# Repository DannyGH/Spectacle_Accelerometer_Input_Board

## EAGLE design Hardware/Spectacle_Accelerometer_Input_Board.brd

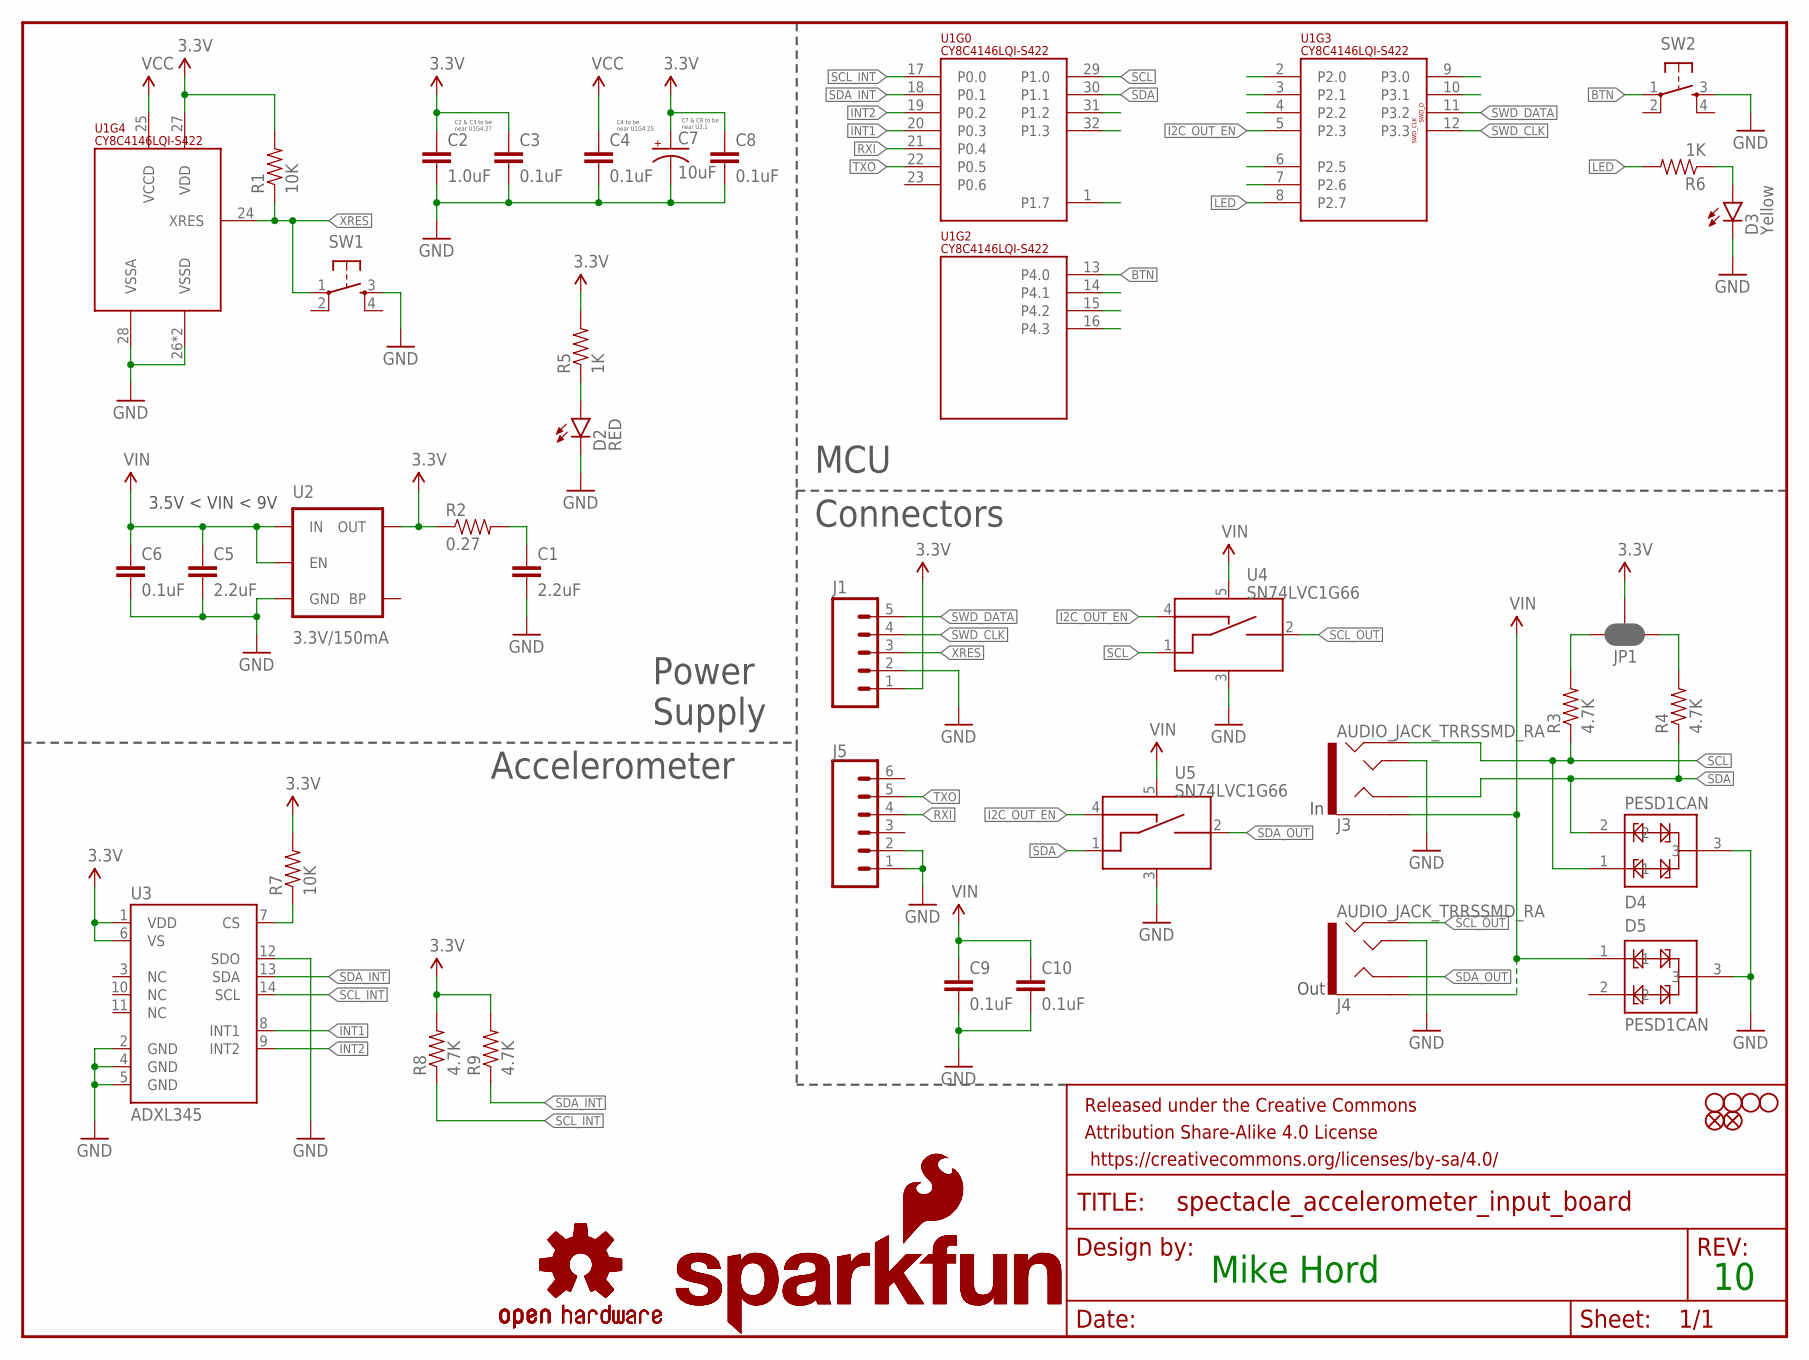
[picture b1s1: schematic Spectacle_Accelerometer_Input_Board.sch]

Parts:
C1, C5: 2.2uF; 0603-CAP
C2: 1.0uF; 0402-CAP
C3, C4, C6, C8, C9, C10: 0.1uF; 0402-CAP
C7: 10uF; EIA3216
D2: RED; LED-0603
D3: Yellow; LED-0603
D4, D5: PESD1CAN; SOT23-3
FD1, FD2: FIDUCIALUFIDUCIAL; MICRO-FIDUCIAL
FRAME1: FRAME-LETTER; CREATIVE_COMMONS
H1, H2, H3, H4: STAND-OFF
J1: M05NO_SILK; 1X05_NO_SILK
J3, J4: AUDIO_JACK_TRRSSMD_RA; AUDIO_JACK_3.5MM_TRRS_SMD_RA
J5: CONN_06NO_SILK_NO_POP; 1X06_NO_SILK
JP1: JUMPER-PAD-3-NC_BY_PASTE; PAD-JUMPER-3-NC_BY_PASTE_YES_SILK_FULL_BOX
LOGO1, LOGO4: SFE_LOGO_NAME_FLAME.1_INCH; SFE_LOGO_NAME_FLAME_.1
LOGO2, LOGO3: OSHW-LOGOS; OSHW-LOGO-S
R1, R7: 10K; 0603-RES
R2: 0.27; 0603-RES
R3, R4, R8, R9: 4.7K; 0603-RES
R5, R6: 1K; 0603-RES
SW1, SW2: SWITCH_SPST_4_PINRECT; TACTILE_SWITCH_SMD_4.6X2.8MM
U1: CY8C4146LQI-S422; QFN-32
U2: 3.3V/150mA; SOT23-5
U3: ADXL345; ADXL3451:1
U4, U5: SN74LVC1G66; SOT23-5

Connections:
3.3V: C2.1, C3.1, C7.A (+), C8.1, J1.1, JP1.2, R1.2, R2.1, R5.2, R7.2, R8.2, R9.2, U1.27 (VDD), U2.5 (OUT), U3.1 (VDD), U3.6 (VS)
BTN: SW2.1, U1.13 (P4.0)
GND: C1.2, C2.2, C3.2, C4.2, C5.2, C6.2, C7.C (-), C8.2, C9.2, C10.2, D2.C, D3.C, D4.3, D5.3, J1.2, J3.TIP, J4.TIP, J5.1, J5.2, SW1.3, SW2.3, U1.26 (VSSD), U1.28 (VSSA), U1.EP (VSSD), U2.2 (GND), U3.2 (GND), U3.4 (GND), U3.5 (GND), U3.12 (SDO), U4.3 (VSS), U5.3 (VSS)
I2C_OUT_EN: U1.5 (P2.3), U4.4 (CTRL_IN), U5.4 (CTRL_IN)
INT1: U1.20 (P0.3), U3.8 (INT1)
INT2: U1.19 (P0.2), U3.9 (INT2)
LED: R6.2, U1.8 (P2.7)
unnamed: JP1.3, R3.2
unnamed: C1.1, R2.2
unnamed: D2.A, R5.1
unnamed: D3.A, R6.1
unnamed: JP1.1, R4.2
unnamed: R7.1, U3.7 (CS)
RXI: J5.4, U1.21 (P0.4)
SCL: D4.1, J3.RING2, R3.1, U1.29 (P1.0), U4.1 (A_IN)
SCL_INT: R8.1, U1.17 (P0.0), U3.14 (SCL)
SCL_OUT: J4.RING2, U4.2 (A_OUT)
SDA: D4.2, J3.RING1, R4.1, U1.30 (P1.1), U5.1 (A_IN)
SDA_INT: R9.1, U1.18 (P0.1), U3.13 (SDA)
SDA_OUT: J4.RING1, U5.2 (A_OUT)
SWD_CLK: J1.4, U1.12 (P3.3)
SWD_DATA: J1.5, U1.11 (P3.2)
TXO: J5.5, U1.22 (P0.5)
VCC: C4.1, U1.25 (VCCD)
VIN: C5.1, C6.1, C9.1, C10.1, D5.1, J3.EARTH, J4.EARTH, U2.1 (IN), U2.3 (EN), U4.5 (VCC), U5.5 (VCC)
XRES: J1.3, R1.1, SW1.1, U1.24 (XRES)

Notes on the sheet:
C2 & C3 to be near U1G4.27
C4 to be near U1G4.25
C7 & C8 to be near U3.1
Mike Hord
Connectors
Accelerometer
MCU
Power Supply
3.5V < VIN < 9V
Out

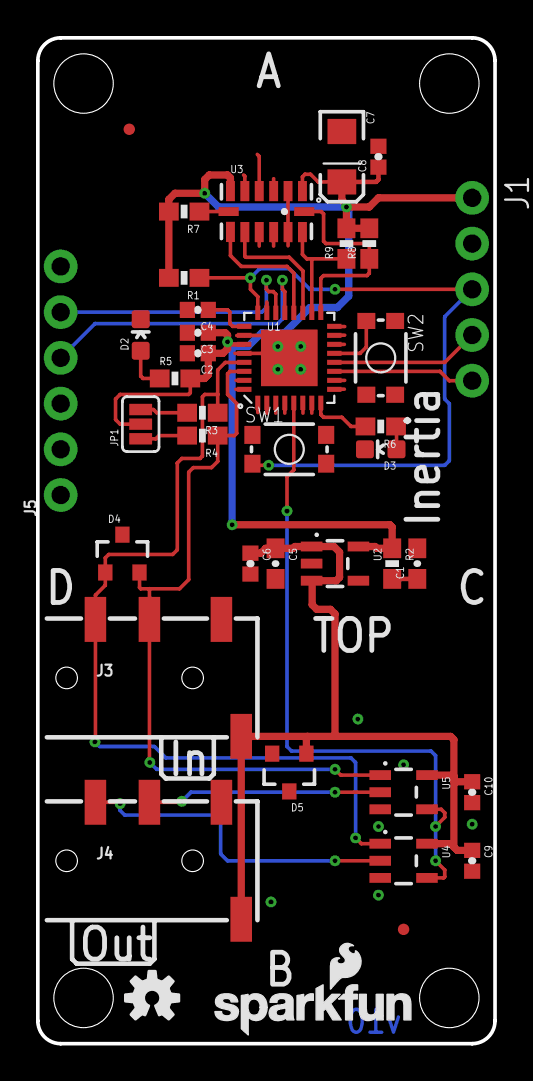
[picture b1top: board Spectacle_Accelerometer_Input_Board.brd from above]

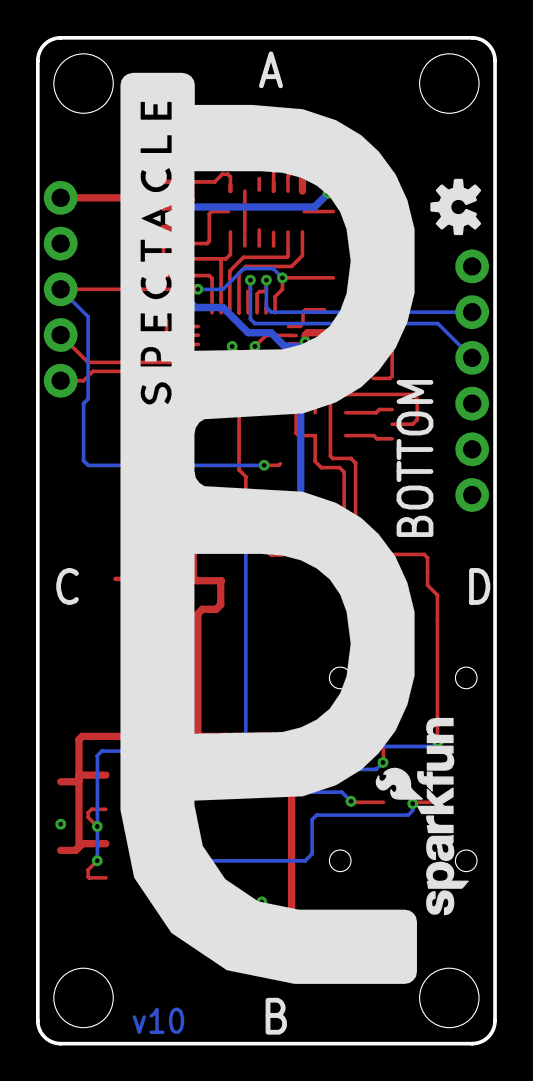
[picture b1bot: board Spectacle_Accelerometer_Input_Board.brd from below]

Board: 2 copper layers, 25.4 x 55.9 mm, 47 parts (3 on the bottom side), 26 nets.

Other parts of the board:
U$4: SPECTACLE_LOGO_NEGATIVE_2.2X1.0

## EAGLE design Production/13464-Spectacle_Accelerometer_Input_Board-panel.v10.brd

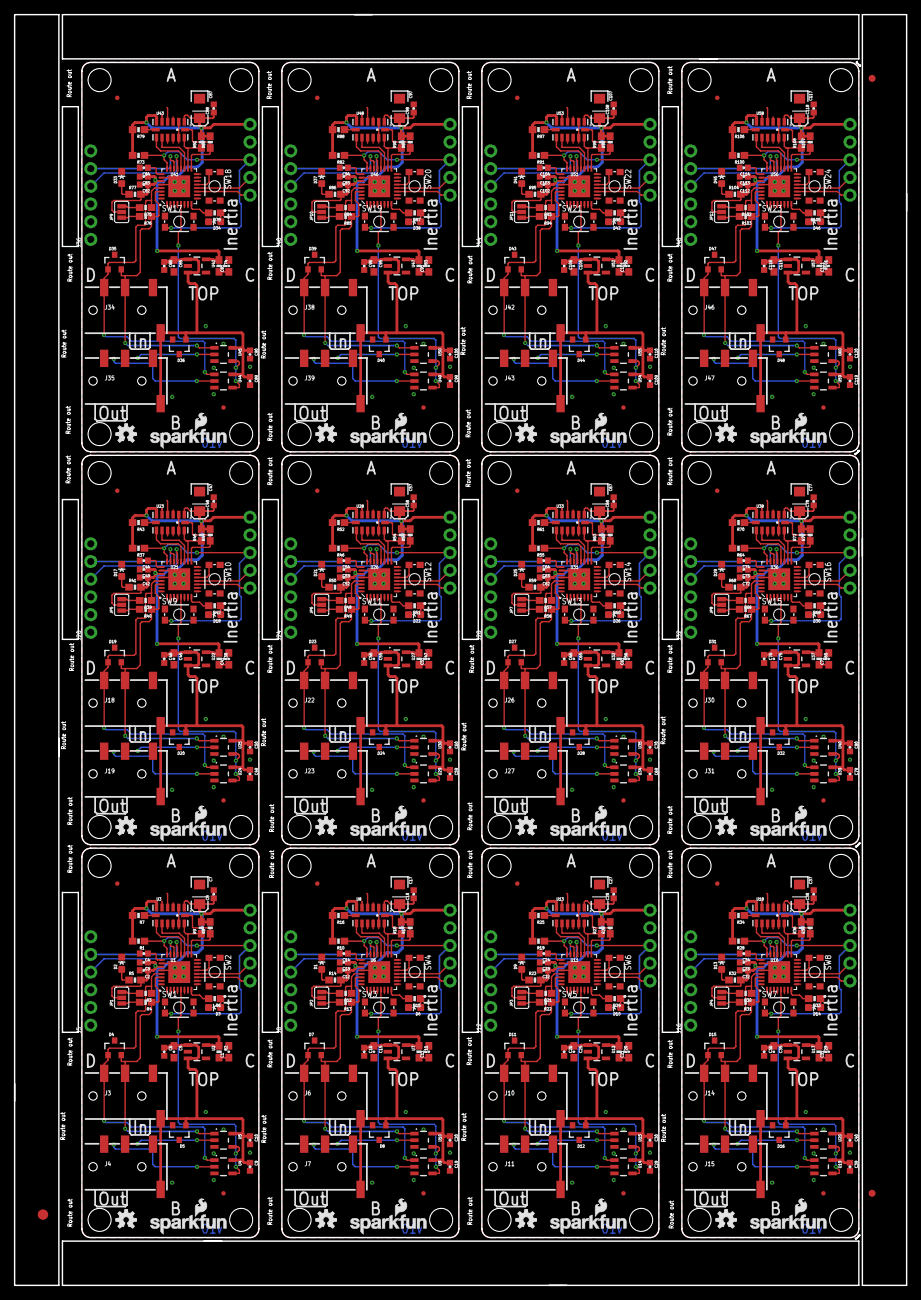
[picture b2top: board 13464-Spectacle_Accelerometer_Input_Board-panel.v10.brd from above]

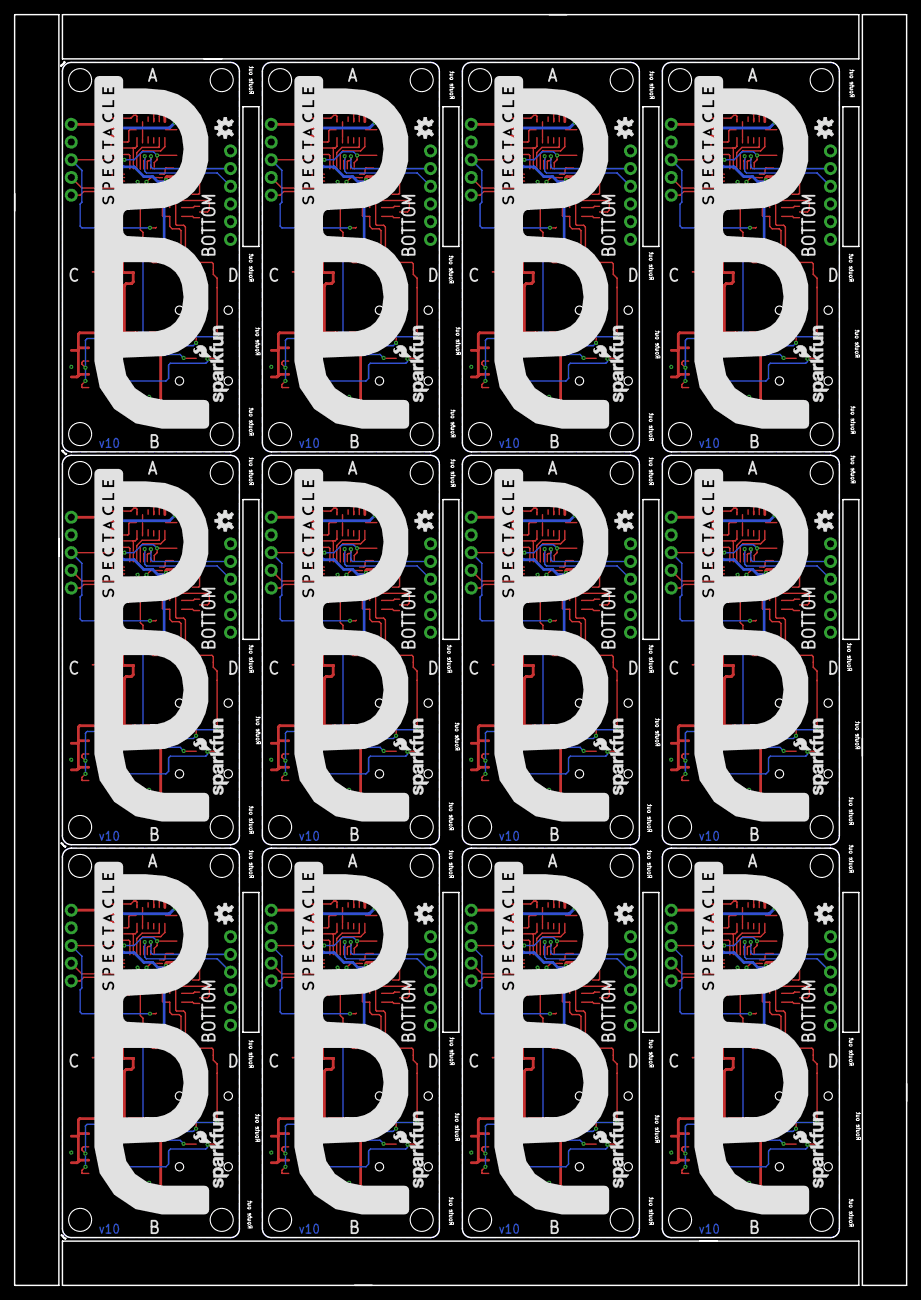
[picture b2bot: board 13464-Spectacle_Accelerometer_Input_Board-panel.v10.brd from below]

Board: 2 copper layers, 128.0 x 182.4 mm, 555 parts (36 on the bottom side), 312 nets.

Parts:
C1, C5, C11, C15, C21, C25, C31, C35, C41, C45, C51, C55, C61, C65, C71, C75, C81, C85, C91, C95, C101, C105, C111, C115: 2.2uF; 0603-CAP
C2, C12, C22, C32, C42, C52, C62, C72, C82, C92, C102, C112: 1.0uF; 0402-CAP
C3, C4, C6, C8, C9, C10, C13, C14, C16, C18, C19, C20, C23, C24, C26, C28, C29, C30, C33, C34, C36, C38, C39, C40, C43, C44, C46, C48, C49, C50, C53, C54, C56, C58, C59, C60, C63, C64, C66, C68, C69, C70, C73, C74, C76, C78, C79, C80, C83, C84, C86, C88, C89, C90, C93, C94, C96, C98, C99, C100, C103, C104, C106, C108, C109, C110, C113, C114, C116, C118, C119, C120: 0.1uF; 0402-CAP
C7, C17, C27, C37, C47, C57, C67, C77, C87, C97, C107, C117: 10uF; EIA3216
D1, D2, D9, D13, D17, D21, D25, D29, D33, D37, D41, D45: RED; LED-0603
D3, D6, D10, D14, D18, D22, D26, D30, D34, D38, D42, D46: Yellow; LED-0603
D4, D5, D7, D8, D11, D12, D15, D16, D19, D20, D23, D24, D27, D28, D31, D32, D35, D36, D39, D40, D43, D44, D47, D48: PESD1CAN; SOT23-3
E$1: FIDUCIAL-1.5X3
E$5, E$6: FIDUCIAL-1X2
FD1, FD2, FD3, FD4, FD5, FD6, FD7, FD8, FD9, FD10, FD11, FD12, FD13, FD14, FD15, FD16, FD17, FD18, FD19, FD20, FD21, FD22, FD23, FD24: FIDUCIALUFIDUCIAL; MICRO-FIDUCIAL
H1, H2, H3, H4, H5, H6, H7, H8, H9, H10, H11, H12, H13, H14, H15, H16, H17, H18, H19, H20, H21, H22, H23, H24, H25, H26, H27, H28, H29, H30, H31, H32, H33, H34, H35, H36, H37, H38, H39, H40, H41, H42, H43, H44, H45, H46, H47, H48: STAND-OFF
J1, J2, J9, J13, J17, J21, J25, J29, J33, J37, J41, J45: 1X05_NO_SILK
J3, J4, J6, J7, J10, J11, J14, J15, J18, J19, J22, J23, J26, J27, J30, J31, J34, J35, J38, J39, J42, J43, J46, J47: AUDIO_JACK_TRRSSMD_RA; AUDIO_JACK_3.5MM_TRRS_SMD_RA
J5, J8, J12, J16, J20, J24, J28, J32, J36, J40, J44, J48: 1X06_NO_SILK
JP1, JP2, JP3, JP4, JP5, JP6, JP7, JP8, JP9, JP10, JP11, JP12: JUMPER-PAD-3-NC_BY_PASTE; PAD-JUMPER-3-NC_BY_PASTE_YES_SILK_FULL_BOX
LOGO1, LOGO4, LOGO5, LOGO8, LOGO9, LOGO12, LOGO13, LOGO16, LOGO17, LOGO20, LOGO21, LOGO24, LOGO25, LOGO28, LOGO29, LOGO32, LOGO33, LOGO36, LOGO37, LOGO40, LOGO41, LOGO44, LOGO45, LOGO48: SFE_LOGO_NAME_FLAME.1_INCH; SFE_LOGO_NAME_FLAME_.1
LOGO2, LOGO3, LOGO6, LOGO7, LOGO10, LOGO11, LOGO14, LOGO15, LOGO18, LOGO19, LOGO22, LOGO23, LOGO26, LOGO27, LOGO30, LOGO31, LOGO34, LOGO35, LOGO38, LOGO39, LOGO42, LOGO43, LOGO46, LOGO47: OSHW-LOGOS; OSHW-LOGO-S
R1, R7, R10, R16, R19, R25, R28, R34, R37, R43, R46, R52, R55, R61, R64, R70, R73, R79, R82, R88, R91, R97, R100, R106: 10K; 0603-RES
R2, R11, R20, R29, R38, R47, R56, R65, R74, R83, R92, R101: 0.27; 0603-RES
R3, R4, R8, R9, R12, R13, R17, R18, R21, R22, R26, R27, R30, R31, R35, R36, R39, R40, R44, R45, R48, R49, R53, R54, R57, R58, R62, R63, R66, R67, R71, R72, R75, R76, R80, R81, R84, R85, R89, R90, R93, R94, R98, R99, R102, R103, R107, R108: 4.7K; 0603-RES
R5, R6, R14, R15, R23, R24, R32, R33, R41, R42, R50, R51, R59, R60, R68, R69, R77, R78, R86, R87, R95, R96, R104, R105: 1K; 0603-RES
SW1, SW2, SW3, SW4, SW5, SW6, SW7, SW8, SW9, SW10, SW11, SW12, SW13, SW14, SW15, SW16, SW17, SW18, SW19, SW20, SW21, SW22, SW23, SW24: TACTILE_SWITCH_SMD_4.6X2.8MM
U1, U6, U11, U16, U21, U26, U31, U36, U41, U46, U51, U56: CY8C4146LQI-S422; QFN-32
U2, U7, U12, U17, U22, U27, U32, U37, U42, U47, U52, U57: 3.3V/150mA; SOT23-5
U3, U8, U13, U18, U23, U28, U33, U38, U43, U48, U53, U58: ADXL345; ADXL3451:1
U4, U5, U9, U10, U14, U15, U19, U20, U24, U25, U29, U30, U34, U35, U39, U40, U44, U45, U49, U50, U54, U55, U59, U60: SN74LVC1G66; SOT23-5
U$1, U$2, U$3, U$4, U$5, U$6, U$7, U$8, U$9, U$10, U$11, U$12: SPECTACLE_LOGO_NEGATIVE_2.2X1.0

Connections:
3.3V: C2.1, C3.1, C7.A, C8.1, J1.1, JP1.2, R1.2, R2.1, R5.2, R7.2, R8.2, R9.2, U1.27, U2.5, U3.1, U3.6
3.3V1: C12.1, C13.1, C17.A, C18.1, J2.1, JP2.2, R10.2, R11.1, R14.2, R16.2, R17.2, R18.2, U6.27, U7.5, U8.1, U8.6
3.3V2: C22.1, C23.1, C27.A, C28.1, J9.1, JP3.2, R19.2, R20.1, R23.2, R25.2, R26.2, R27.2, U11.27, U12.5, U13.1, U13.6
3.3V3: C32.1, C33.1, C37.A, C38.1, J13.1, JP4.2, R28.2, R29.1, R32.2, R34.2, R35.2, R36.2, U16.27, U17.5, U18.1, U18.6
3.3V4: C42.1, C43.1, C47.A, C48.1, J17.1, JP5.2, R37.2, R38.1, R41.2, R43.2, R44.2, R45.2, U21.27, U22.5, U23.1, U23.6
3.3V5: C52.1, C53.1, C57.A, C58.1, J21.1, JP6.2, R46.2, R47.1, R50.2, R52.2, R53.2, R54.2, U26.27, U27.5, U28.1, U28.6
3.3V6: C62.1, C63.1, C67.A, C68.1, J25.1, JP7.2, R55.2, R56.1, R59.2, R61.2, R62.2, R63.2, U31.27, U32.5, U33.1, U33.6
3.3V7: C72.1, C73.1, C77.A, C78.1, J29.1, JP8.2, R64.2, R65.1, R68.2, R70.2, R71.2, R72.2, U36.27, U37.5, U38.1, U38.6
3.3V8: C82.1, C83.1, C87.A, C88.1, J33.1, JP9.2, R73.2, R74.1, R77.2, R79.2, R80.2, R81.2, U41.27, U42.5, U43.1, U43.6
3.3V9: C92.1, C93.1, C97.A, C98.1, J37.1, JP10.2, R82.2, R83.1, R86.2, R88.2, R89.2, R90.2, U46.27, U47.5, U48.1, U48.6
3.3V10: C102.1, C103.1, C107.A, C108.1, J41.1, JP11.2, R91.2, R92.1, R95.2, R97.2, R98.2, R99.2, U51.27, U52.5, U53.1, U53.6
3.3V11: C112.1, C113.1, C117.A, C118.1, J45.1, JP12.2, R100.2, R101.1, R104.2, R106.2, R107.2, R108.2, U56.27, U57.5, U58.1, U58.6
BTN: SW2.1, U1.13
BTN1: SW4.1, U6.13
BTN2: SW6.1, U11.13
BTN3: SW8.1, U16.13
BTN4: SW10.1, U21.13
BTN5: SW12.1, U26.13
BTN6: SW14.1, U31.13
BTN7: SW16.1, U36.13
BTN8: SW18.1, U41.13
BTN9: SW20.1, U46.13
BTN10: SW22.1, U51.13
BTN11: SW24.1, U56.13
GND: C1.2, C2.2, C3.2, C4.2, C5.2, C6.2, C7.C, C8.2, C9.2, C10.2, D2.C, D3.C, D4.3, D5.3, J1.2, J3.TIP, J4.TIP, J5.1, J5.2, SW1.3, SW2.3, U1.26, U1.28, U1.EP, U2.2, U3.2, U3.4, U3.5, U3.12, U4.3, U5.3
GND1: C11.2, C12.2, C13.2, C14.2, C15.2, C16.2, C17.C, C18.2, C19.2, C20.2, D1.C, D6.C, D7.3, D8.3, J2.2, J6.TIP, J7.TIP, J8.1, J8.2, SW3.3, SW4.3, U6.26, U6.28, U6.EP, U7.2, U8.2, U8.4, U8.5, U8.12, U9.3, U10.3
GND2: C21.2, C22.2, C23.2, C24.2, C25.2, C26.2, C27.C, C28.2, C29.2, C30.2, D9.C, D10.C, D11.3, D12.3, J9.2, J10.TIP, J11.TIP, J12.1, J12.2, SW5.3, SW6.3, U11.26, U11.28, U11.EP, U12.2, U13.2, U13.4, U13.5, U13.12, U14.3, U15.3
GND3: C31.2, C32.2, C33.2, C34.2, C35.2, C36.2, C37.C, C38.2, C39.2, C40.2, D13.C, D14.C, D15.3, D16.3, J13.2, J14.TIP, J15.TIP, J16.1, J16.2, SW7.3, SW8.3, U16.26, U16.28, U16.EP, U17.2, U18.2, U18.4, U18.5, U18.12, U19.3, U20.3
GND4: C41.2, C42.2, C43.2, C44.2, C45.2, C46.2, C47.C, C48.2, C49.2, C50.2, D17.C, D18.C, D19.3, D20.3, J17.2, J18.TIP, J19.TIP, J20.1, J20.2, SW9.3, SW10.3, U21.26, U21.28, U21.EP, U22.2, U23.2, U23.4, U23.5, U23.12, U24.3, U25.3
GND5: C51.2, C52.2, C53.2, C54.2, C55.2, C56.2, C57.C, C58.2, C59.2, C60.2, D21.C, D22.C, D23.3, D24.3, J21.2, J22.TIP, J23.TIP, J24.1, J24.2, SW11.3, SW12.3, U26.26, U26.28, U26.EP, U27.2, U28.2, U28.4, U28.5, U28.12, U29.3, U30.3
GND6: C61.2, C62.2, C63.2, C64.2, C65.2, C66.2, C67.C, C68.2, C69.2, C70.2, D25.C, D26.C, D27.3, D28.3, J25.2, J26.TIP, J27.TIP, J28.1, J28.2, SW13.3, SW14.3, U31.26, U31.28, U31.EP, U32.2, U33.2, U33.4, U33.5, U33.12, U34.3, U35.3
GND7: C71.2, C72.2, C73.2, C74.2, C75.2, C76.2, C77.C, C78.2, C79.2, C80.2, D29.C, D30.C, D31.3, D32.3, J29.2, J30.TIP, J31.TIP, J32.1, J32.2, SW15.3, SW16.3, U36.26, U36.28, U36.EP, U37.2, U38.2, U38.4, U38.5, U38.12, U39.3, U40.3
GND8: C81.2, C82.2, C83.2, C84.2, C85.2, C86.2, C87.C, C88.2, C89.2, C90.2, D33.C, D34.C, D35.3, D36.3, J33.2, J34.TIP, J35.TIP, J36.1, J36.2, SW17.3, SW18.3, U41.26, U41.28, U41.EP, U42.2, U43.2, U43.4, U43.5, U43.12, U44.3, U45.3
GND9: C91.2, C92.2, C93.2, C94.2, C95.2, C96.2, C97.C, C98.2, C99.2, C100.2, D37.C, D38.C, D39.3, D40.3, J37.2, J38.TIP, J39.TIP, J40.1, J40.2, SW19.3, SW20.3, U46.26, U46.28, U46.EP, U47.2, U48.2, U48.4, U48.5, U48.12, U49.3, U50.3
GND10: C101.2, C102.2, C103.2, C104.2, C105.2, C106.2, C107.C, C108.2, C109.2, C110.2, D41.C, D42.C, D43.3, D44.3, J41.2, J42.TIP, J43.TIP, J44.1, J44.2, SW21.3, SW22.3, U51.26, U51.28, U51.EP, U52.2, U53.2, U53.4, U53.5, U53.12, U54.3, U55.3
GND11: C111.2, C112.2, C113.2, C114.2, C115.2, C116.2, C117.C, C118.2, C119.2, C120.2, D45.C, D46.C, D47.3, D48.3, J45.2, J46.TIP, J47.TIP, J48.1, J48.2, SW23.3, SW24.3, U56.26, U56.28, U56.EP, U57.2, U58.2, U58.4, U58.5, U58.12, U59.3, U60.3
I2C_OUT_EN: U1.5, U4.4, U5.4
I2C_OUT_EN1: U6.5, U9.4, U10.4
I2C_OUT_EN2: U11.5, U14.4, U15.4
I2C_OUT_EN3: U16.5, U19.4, U20.4
I2C_OUT_EN4: U21.5, U24.4, U25.4
I2C_OUT_EN5: U26.5, U29.4, U30.4
I2C_OUT_EN6: U31.5, U34.4, U35.4
I2C_OUT_EN7: U36.5, U39.4, U40.4
I2C_OUT_EN8: U41.5, U44.4, U45.4
I2C_OUT_EN9: U46.5, U49.4, U50.4
I2C_OUT_EN10: U51.5, U54.4, U55.4
I2C_OUT_EN11: U56.5, U59.4, U60.4
INT1: U1.20, U3.8
INT2: U1.19, U3.9
INT3: U6.20, U8.8
INT4: U6.19, U8.9
INT5: U11.20, U13.8
INT6: U11.19, U13.9
INT7: U16.20, U18.8
INT8: U16.19, U18.9
INT9: U21.20, U23.8
INT10: U21.19, U23.9
INT11: U26.20, U28.8
INT12: U26.19, U28.9
INT13: U31.20, U33.8
INT14: U31.19, U33.9
INT15: U36.20, U38.8
INT16: U36.19, U38.9
INT17: U41.20, U43.8
INT18: U41.19, U43.9
INT19: U46.20, U48.8
INT20: U46.19, U48.9
INT21: U51.20, U53.8
INT22: U51.19, U53.9
INT23: U56.20, U58.8
INT24: U56.19, U58.9
LED: R6.2, U1.8
LED1: R15.2, U6.8
LED2: R24.2, U11.8
LED3: R33.2, U16.8
LED4: R42.2, U21.8
LED5: R51.2, U26.8
LED6: R60.2, U31.8
LED7: R69.2, U36.8
LED8: R78.2, U41.8
LED9: R87.2, U46.8
LED10: R96.2, U51.8
LED11: R105.2, U56.8
unnamed: JP1.3, R3.2
unnamed: C1.1, R2.2
unnamed: D2.A, R5.1
unnamed: D3.A, R6.1
unnamed: JP1.1, R4.2
unnamed: R7.1, U3.7
unnamed: C11.1, R11.2
unnamed: JP2.3, R12.2
unnamed: JP2.1, R13.2
unnamed: D1.A, R14.1
unnamed: D6.A, R15.1
unnamed: R16.1, U8.7
unnamed: C21.1, R20.2
unnamed: JP3.3, R21.2
unnamed: JP3.1, R22.2
unnamed: D9.A, R23.1
unnamed: D10.A, R24.1
unnamed: R25.1, U13.7
unnamed: C31.1, R29.2
unnamed: JP4.3, R30.2
unnamed: JP4.1, R31.2
unnamed: D13.A, R32.1
unnamed: D14.A, R33.1
unnamed: R34.1, U18.7
unnamed: C41.1, R38.2
unnamed: JP5.3, R39.2
unnamed: JP5.1, R40.2
unnamed: D17.A, R41.1
unnamed: D18.A, R42.1
unnamed: R43.1, U23.7
unnamed: C51.1, R47.2
unnamed: JP6.3, R48.2
unnamed: JP6.1, R49.2
unnamed: D21.A, R50.1
unnamed: D22.A, R51.1
unnamed: R52.1, U28.7
unnamed: C61.1, R56.2
unnamed: JP7.3, R57.2
unnamed: JP7.1, R58.2
unnamed: D25.A, R59.1
unnamed: D26.A, R60.1
unnamed: R61.1, U33.7
unnamed: C71.1, R65.2
unnamed: JP8.3, R66.2
unnamed: JP8.1, R67.2
unnamed: D29.A, R68.1
unnamed: D30.A, R69.1
unnamed: R70.1, U38.7
unnamed: C81.1, R74.2
unnamed: JP9.3, R75.2
unnamed: JP9.1, R76.2
unnamed: D33.A, R77.1
unnamed: D34.A, R78.1
unnamed: R79.1, U43.7
unnamed: C91.1, R83.2
unnamed: JP10.3, R84.2
unnamed: JP10.1, R85.2
unnamed: D37.A, R86.1
unnamed: D38.A, R87.1
unnamed: R88.1, U48.7
unnamed: C101.1, R92.2
unnamed: JP11.3, R93.2
unnamed: JP11.1, R94.2
unnamed: D41.A, R95.1
unnamed: D42.A, R96.1
unnamed: R97.1, U53.7
unnamed: C111.1, R101.2
unnamed: JP12.3, R102.2
unnamed: JP12.1, R103.2
unnamed: D45.A, R104.1
unnamed: D46.A, R105.1
unnamed: R106.1, U58.7
RXI: J5.4, U1.21
RXI1: J8.4, U6.21
RXI2: J12.4, U11.21
RXI3: J16.4, U16.21
RXI4: J20.4, U21.21
RXI5: J24.4, U26.21
RXI6: J28.4, U31.21
RXI7: J32.4, U36.21
RXI8: J36.4, U41.21
RXI9: J40.4, U46.21
RXI10: J44.4, U51.21
RXI11: J48.4, U56.21
SCL: D4.1, J3.RING2, R3.1, U1.29, U4.1
SCL1: D7.1, J6.RING2, R12.1, U6.29, U9.1
SCL2: D11.1, J10.RING2, R21.1, U11.29, U14.1
SCL3: D15.1, J14.RING2, R30.1, U16.29, U19.1
SCL4: D19.1, J18.RING2, R39.1, U21.29, U24.1
SCL5: D23.1, J22.RING2, R48.1, U26.29, U29.1
SCL6: D27.1, J26.RING2, R57.1, U31.29, U34.1
SCL7: D31.1, J30.RING2, R66.1, U36.29, U39.1
SCL8: D35.1, J34.RING2, R75.1, U41.29, U44.1
SCL9: D39.1, J38.RING2, R84.1, U46.29, U49.1
SCL10: D43.1, J42.RING2, R93.1, U51.29, U54.1
SCL11: D47.1, J46.RING2, R102.1, U56.29, U59.1
SCL_INT: R8.1, U1.17, U3.14
SCL_INT1: R17.1, U6.17, U8.14
SCL_INT2: R26.1, U11.17, U13.14
SCL_INT3: R35.1, U16.17, U18.14
SCL_INT4: R44.1, U21.17, U23.14
SCL_INT5: R53.1, U26.17, U28.14
SCL_INT6: R62.1, U31.17, U33.14
SCL_INT7: R71.1, U36.17, U38.14
SCL_INT8: R80.1, U41.17, U43.14
SCL_INT9: R89.1, U46.17, U48.14
SCL_INT10: R98.1, U51.17, U53.14
SCL_INT11: R107.1, U56.17, U58.14
SCL_OUT: J4.RING2, U4.2
SCL_OUT1: J7.RING2, U9.2
SCL_OUT2: J11.RING2, U14.2
SCL_OUT3: J15.RING2, U19.2
SCL_OUT4: J19.RING2, U24.2
SCL_OUT5: J23.RING2, U29.2
SCL_OUT6: J27.RING2, U34.2
SCL_OUT7: J31.RING2, U39.2
SCL_OUT8: J35.RING2, U44.2
SCL_OUT9: J39.RING2, U49.2
SCL_OUT10: J43.RING2, U54.2
SCL_OUT11: J47.RING2, U59.2
SDA: D4.2, J3.RING1, R4.1, U1.30, U5.1
SDA1: D7.2, J6.RING1, R13.1, U6.30, U10.1
SDA2: D11.2, J10.RING1, R22.1, U11.30, U15.1
SDA3: D15.2, J14.RING1, R31.1, U16.30, U20.1
SDA4: D19.2, J18.RING1, R40.1, U21.30, U25.1
SDA5: D23.2, J22.RING1, R49.1, U26.30, U30.1
SDA6: D27.2, J26.RING1, R58.1, U31.30, U35.1
SDA7: D31.2, J30.RING1, R67.1, U36.30, U40.1
SDA8: D35.2, J34.RING1, R76.1, U41.30, U45.1
SDA9: D39.2, J38.RING1, R85.1, U46.30, U50.1
SDA10: D43.2, J42.RING1, R94.1, U51.30, U55.1
SDA11: D47.2, J46.RING1, R103.1, U56.30, U60.1
SDA_INT: R9.1, U1.18, U3.13
SDA_INT1: R18.1, U6.18, U8.13
SDA_INT2: R27.1, U11.18, U13.13
SDA_INT3: R36.1, U16.18, U18.13
SDA_INT4: R45.1, U21.18, U23.13
SDA_INT5: R54.1, U26.18, U28.13
SDA_INT6: R63.1, U31.18, U33.13
SDA_INT7: R72.1, U36.18, U38.13
SDA_INT8: R81.1, U41.18, U43.13
SDA_INT9: R90.1, U46.18, U48.13
SDA_INT10: R99.1, U51.18, U53.13
SDA_INT11: R108.1, U56.18, U58.13
SDA_OUT: J4.RING1, U5.2
SDA_OUT1: J7.RING1, U10.2
SDA_OUT2: J11.RING1, U15.2
SDA_OUT3: J15.RING1, U20.2
SDA_OUT4: J19.RING1, U25.2
SDA_OUT5: J23.RING1, U30.2
SDA_OUT6: J27.RING1, U35.2
SDA_OUT7: J31.RING1, U40.2
SDA_OUT8: J35.RING1, U45.2
SDA_OUT9: J39.RING1, U50.2
SDA_OUT10: J43.RING1, U55.2
SDA_OUT11: J47.RING1, U60.2
SWD_CLK: J1.4, U1.12
SWD_CLK1: J2.4, U6.12
SWD_CLK2: J9.4, U11.12
SWD_CLK3: J13.4, U16.12
SWD_CLK4: J17.4, U21.12
SWD_CLK5: J21.4, U26.12
SWD_CLK6: J25.4, U31.12
SWD_CLK7: J29.4, U36.12
SWD_CLK8: J33.4, U41.12
SWD_CLK9: J37.4, U46.12
SWD_CLK10: J41.4, U51.12
SWD_CLK11: J45.4, U56.12
SWD_DATA: J1.5, U1.11
SWD_DATA1: J2.5, U6.11
SWD_DATA2: J9.5, U11.11
SWD_DATA3: J13.5, U16.11
SWD_DATA4: J17.5, U21.11
SWD_DATA5: J21.5, U26.11
SWD_DATA6: J25.5, U31.11
SWD_DATA7: J29.5, U36.11
SWD_DATA8: J33.5, U41.11
SWD_DATA9: J37.5, U46.11
SWD_DATA10: J41.5, U51.11
SWD_DATA11: J45.5, U56.11
TXO: J5.5, U1.22
TXO1: J8.5, U6.22
TXO2: J12.5, U11.22
TXO3: J16.5, U16.22
TXO4: J20.5, U21.22
TXO5: J24.5, U26.22
TXO6: J28.5, U31.22
TXO7: J32.5, U36.22
TXO8: J36.5, U41.22
TXO9: J40.5, U46.22
TXO10: J44.5, U51.22
TXO11: J48.5, U56.22
VCC: C4.1, U1.25
VCC1: C14.1, U6.25
VCC2: C24.1, U11.25
VCC3: C34.1, U16.25
VCC4: C44.1, U21.25
VCC5: C54.1, U26.25
VCC6: C64.1, U31.25
VCC7: C74.1, U36.25
VCC8: C84.1, U41.25
VCC9: C94.1, U46.25
VCC10: C104.1, U51.25
VCC11: C114.1, U56.25
VIN: C5.1, C6.1, C9.1, C10.1, D5.1, J3.EARTH, J4.EARTH, U2.1, U2.3, U4.5, U5.5
VIN1: C15.1, C16.1, C19.1, C20.1, D8.1, J6.EARTH, J7.EARTH, U7.1, U7.3, U9.5, U10.5
VIN2: C25.1, C26.1, C29.1, C30.1, D12.1, J10.EARTH, J11.EARTH, U12.1, U12.3, U14.5, U15.5
VIN3: C35.1, C36.1, C39.1, C40.1, D16.1, J14.EARTH, J15.EARTH, U17.1, U17.3, U19.5, U20.5
VIN4: C45.1, C46.1, C49.1, C50.1, D20.1, J18.EARTH, J19.EARTH, U22.1, U22.3, U24.5, U25.5
VIN5: C55.1, C56.1, C59.1, C60.1, D24.1, J22.EARTH, J23.EARTH, U27.1, U27.3, U29.5, U30.5
VIN6: C65.1, C66.1, C69.1, C70.1, D28.1, J26.EARTH, J27.EARTH, U32.1, U32.3, U34.5, U35.5
VIN7: C75.1, C76.1, C79.1, C80.1, D32.1, J30.EARTH, J31.EARTH, U37.1, U37.3, U39.5, U40.5
VIN8: C85.1, C86.1, C89.1, C90.1, D36.1, J34.EARTH, J35.EARTH, U42.1, U42.3, U44.5, U45.5
VIN9: C95.1, C96.1, C99.1, C100.1, D40.1, J38.EARTH, J39.EARTH, U47.1, U47.3, U49.5, U50.5
VIN10: C105.1, C106.1, C109.1, C110.1, D44.1, J42.EARTH, J43.EARTH, U52.1, U52.3, U54.5, U55.5
VIN11: C115.1, C116.1, C119.1, C120.1, D48.1, J46.EARTH, J47.EARTH, U57.1, U57.3, U59.5, U60.5
XRES: J1.3, R1.1, SW1.1, U1.24
XRES1: J2.3, R10.1, SW3.1, U6.24
XRES2: J9.3, R19.1, SW5.1, U11.24
XRES3: J13.3, R28.1, SW7.1, U16.24
XRES4: J17.3, R37.1, SW9.1, U21.24
XRES5: J21.3, R46.1, SW11.1, U26.24
XRES6: J25.3, R55.1, SW13.1, U31.24
XRES7: J29.3, R64.1, SW15.1, U36.24
XRES8: J33.3, R73.1, SW17.1, U41.24
XRES9: J37.3, R82.1, SW19.1, U46.24
XRES10: J41.3, R91.1, SW21.1, U51.24
XRES11: J45.3, R100.1, SW23.1, U56.24

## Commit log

2016-07-15 Derived from button board
2016-07-15 Initial commit of new design files
2016-07-18 Cleared some DRC errors
2016-07-21 Review feedback
2016-07-26 Fixed issues from Eric's review
2016-10-11 Added downstream power control circuitry
2016-10-12 Nice place for a code commit. Has structure of I2C registers in place, along with necessary handlers and updates for new styles.
2016-10-13 Adding firmware
2016-10-13 Added notes to IN and OUT connectors
2016-10-20 Fixes from design review
2016-10-20 Some changes during checklist
2016-10-24 Fixed missing tCream on pad 19 of psoc IC
2016-10-28 I2C disconnect circuitry added
2016-10-31 Change 2.2k I2C pullup to 4.7k Add Arduino test sketch
2016-12-20 Firmware commit All functionality present and passes initial testing.
2017-01-23 Touch-ups for v10 release
2017-01-25 Clean up in preparation for release - Removed a few unneeded files - Added headers to all files
2017-01-25 Reduced config data size
2017-01-25 Update silk to reflect name Inertia
2017-01-26 panel
2017-02-10 Added detect which side is up for sides other than A
2017-04-05 Change UART speed to 9600

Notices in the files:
parts and their libraries:
SparkFun-Aesthetics: Licensing: Creative Commons ShareAlike 4.0 International - https://creativecommons.org/licenses/by-sa/4.0
SparkFun-Aesthetics: Released under the Creative Commons Attribution Share-Alike 4.0 License
SparkFun-Aesthetics: https://creativecommons.org/licenses/by-sa/4.0
